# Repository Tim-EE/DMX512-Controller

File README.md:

# DMX Controller

This repository contains a hardware design for a custom DMX512 controller as well as the corresponding firmware that allows the hardware to be controlled via a serial port on a computer.

## Structure

In this repository, you'll find the following:

| Directory | Description |
| --------- | ----------- |
| `firmware` | Contains the firmware for the DMX controller |
| `hw` | Contains the hardware designs for the DMX controller (KiCad) |
| `tools` | Contains any tools used to assist the design and use of the DMX controller |

## References

* [DMX Explained; DMX512 and RS-485 Protocol Detail for Lighting Applications](https://www.element14.com/community/groups/open-source-hardware/blog/2017/08/24/dmx-explained-dmx512-and-rs-485-protocol-detail-for-lighting-applications)
* [Wikipedia: DMX512](https://en.wikipedia.org/wiki/DMX512)

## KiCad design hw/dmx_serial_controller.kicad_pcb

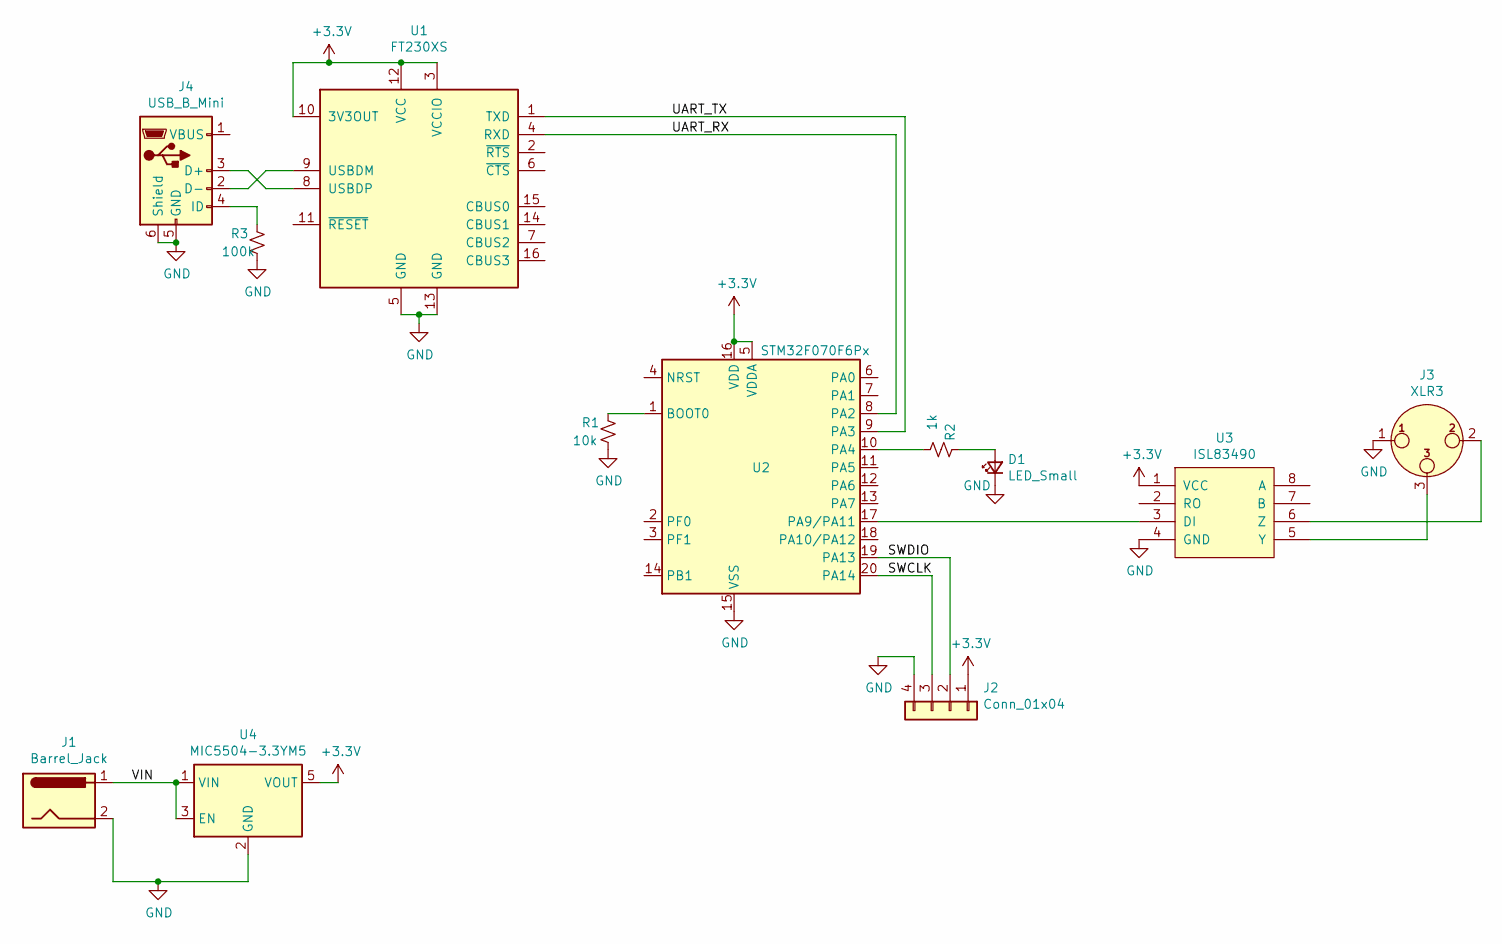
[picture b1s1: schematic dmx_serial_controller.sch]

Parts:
D1: LED_Small; LED_0805_HandSoldering
J1: Barrel_Jack; Pin_Header_Straight_1x02_Pitch2.54mm
J2: Conn_01x04; Pin_Header_Straight_1x04_Pitch2.54mm
J3: XLR3; Pin_Header_Straight_1x03_Pitch2.54mm
J4: USB_B_Mini; USB_Mini-B
R1: 10k; R_0805_HandSoldering
R2: 1k; R_0805_HandSoldering
R3: 100k; R_0805_HandSoldering
U1: FT230XS; SSOP-16_3.9x4.9mm_Pitch0.635mm; digikey# 768-1135-2-ND
U2: STM32F070F6Px; TSSOP-20_4.4x6.5mm_Pitch0.65mm; digikey# 497-17354-1-ND
U3: ISL83490; SOIC-8-N; digikey# ISL83490IBZ-ND
U4: MIC5504-3.3YM5; SOT-23-5; digikey# 576-4764-1-ND

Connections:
+3V3: J2.1, U1.3 (VCCIO), U1.10 (3V3OUT), U1.12 (VCC), U2.5 (VDDA), U2.16 (VDD), U3.1 (VCC), U4.5 (VOUT)
/SWCLK: J2.3, U2.20 (PA14)
/SWDIO: J2.2, U2.19 (PA13)
/UART_RX: U1.4 (RXD), U2.8 (PA2)
/UART_TX: U1.1 (TXD), U2.9 (PA3)
/VIN: J1.1, U4.1 (VIN), U4.3 (EN)
GND: D1.1 (K), J1.2, J2.4, J3.1, J4.5 (GND), J4.6 (Shield), R1.2, R3.2, U1.5 (GND), U1.13 (GND), U2.15 (VSS), U3.4 (GND), U4.2 (GND)
unnamed: D1.2 (A), R2.1
unnamed: J3.2, U3.6 (Z)
unnamed: J3.3, U3.5 (Y)
unnamed: J4.2 (D-), U1.9 (USBDM)
unnamed: J4.3 (D+), U1.8 (USBDP)
unnamed: J4.4 (ID), R3.1
unnamed: R1.1, U2.1 (BOOT0)
unnamed: R2.2, U2.10 (PA4)
unnamed: U2.17 (PA9/PA11), U3.3 (DI)

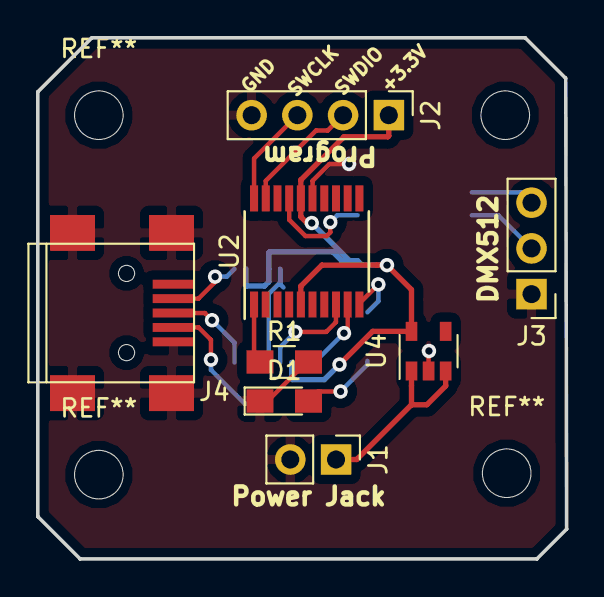
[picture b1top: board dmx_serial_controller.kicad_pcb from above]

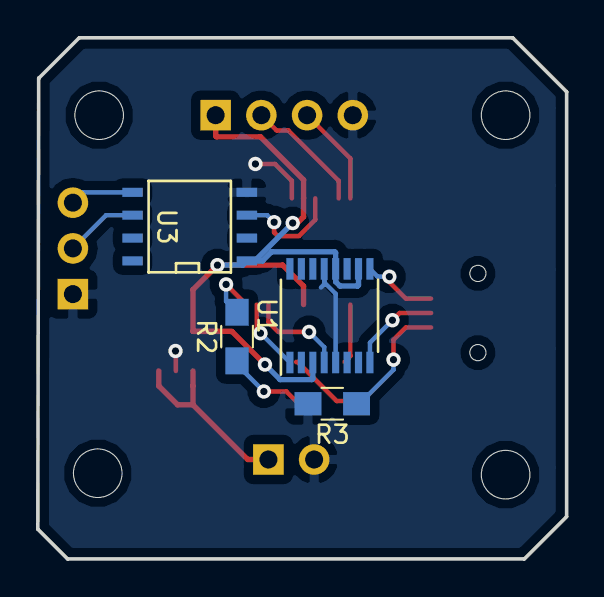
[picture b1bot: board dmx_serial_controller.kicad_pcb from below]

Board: 2 copper layers, 29.4 x 29.0 mm, 12 parts (4 on the bottom side), 16 nets.
